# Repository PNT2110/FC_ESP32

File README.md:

# FC_ESP32 Flight Controller

An ESP32-WROOM-32 based flight controller designed for 1S brushed quadcopters.

## Features
- **MCU**: ESP32-WROOM-32 (8MB Flash)
- **IMU**: MPU-6500 (SPI interface)
- **Motor Drivers**: 4x AO3400 MOSFETs for brushed motors
- **Optical Flow**: UART interface for MTF-01P sensor (JST SH1.0 4-pin)
- **Power**: 1S LiPo input, TPS63001 Buck-Boost for 3.3V, TPS61070 Boost for 5V (USB/Optical flow)
- **USB**: USB-C connector with CH340C USB-to-UART bridge
- **Expansion**: I2C and UART1 breakout headers (2.54mm pitch)
- **Battery Monitor**: Built-in voltage divider for telemetry

## Hardware Setup & Pinout
- **Motors**: J4, J5, J6, J7 pads (AO3400 driven)
- **Optical Flow (J2)**: pin 1 GND, pin 2 +5V_FLOW, pin 3 ESP32 TX (GPIO17 → sensor RX), pin 4 ESP32 RX (GPIO16 ← sensor TX). Verify the actual sensor cable orientation.
- **I2C Expansion (J8)**: VCC, GND, SDA (GPIO4), SCL (GPIO22)
- **UART1 Expansion (J9)**: VCC, GND, TX (GPIO14), RX (GPIO32)
- **Programming**: CH340C DTR/RTS auto-download circuit; no physical Boot/Reset buttons are present in the generated BOM.

## Current status

The subsequent datasheet review found B.Cu tracks inside the ESP32 antenna region,
power-layout concerns and incomplete flight features despite clean ERC/DRC.
See `BAO_CAO_KIEM_TRA_MACH.md` and `validation/datasheet_audit/LOG_KIEM_TRA.md`.
The independent antenna check fails; do not interpret the routing checks below as
proof that the design is ready to operate or manufacture.

PCB routing and final ERC/DRC/parity checks passed on 2026-09-14 (KiCad 10.0.6):
zero violations and zero unconnected items. Motor solder pads moved 1.5 mm inward;
J2 faces outward. See `validation/FINAL_REVIEW.md` and `validation/final_3d.png`.
Not released for manufacturing or flight. Motor pitch is
66.8 mm, prop diameter 40 mm, board thickness 0.8 mm. Components are on the front;
copper routing uses both layers. Firmware motor actuation is disabled by default;
see `firmware/README.md`.

## Reproducible hardware workflow

Use system Python with KiCad 10 `pcbnew`, `sexpdata` and Shapely installed.
The generator replaces the working PCB and therefore discards its routing.
Back up a routed board before regenerating.

```sh
/usr/bin/python3 tools/build_fc.py
/usr/bin/python3 tools/prepare_route.py
# Route the new FC_ESP32/FC_ESP32.dsn with Freerouting and save FC_ESP32.ses.
/usr/bin/python3 tools/import_route.py
/usr/bin/python3 tools/finish_copper.py
python3 tools/validate_fc.py
```

`build_fc.py` now includes clearance-preserving placement and updates the BOM and
design coordinates. Session import validates placement before replacing copper.
The legacy `critical_routes.py` and `repair_connections.py` contain assumptions
from the older layout and are not part of this workflow.

On the current machine, prefix system-Python commands with
`PYTHONPATH=/home/pnt/miniconda3/lib/python3.14/site-packages`.
This path is environment-specific. Generation was verified in an isolated copy;
all 72 component placements, orientations, values, footprints and nets matched.

The current SES predates the final repairs: do not import it onto the final PCB.
`validation/final_routed.kicad_pcb` preserves the reviewed routing.
`tools/repair_c3_ground.py` documents the deterministic final copper repair from
`validation/only_c3_ground_remaining.kicad_pcb` to its candidate output.

Open `FC_ESP32/FC_ESP32.kicad_pro` for review. Validation records current ERC,
DRC, netlist parity and source hashes in `FC_ESP32/validation_summary.json` and
returns nonzero on errors. Reports do not replace current/thermal analysis or
bench testing. `gerbers/` contains stale outputs, not an approved release.

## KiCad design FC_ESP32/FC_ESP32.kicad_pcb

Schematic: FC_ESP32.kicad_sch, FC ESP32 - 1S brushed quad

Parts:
C1, C17: 22uF 10V X5R; C_0805_2012Metric
C2, C4, C5, C7, C9, C15, C18: 100nF; C_0402_1005Metric
C3: 1uF; C_0603_1608Metric
C6: 10nF; C_0402_1005Metric
C8: 1uF; C_0402_1005Metric
C11: 1uF 10V; C_0603_1608Metric
C12, C13: 10uF 10V X5R; C_0805_2012Metric
C19: 47uF 10V X5R; C_1206_3216Metric
C21, C22, C23, C24: 100nF 10V; C_0603_1608Metric
D1, D2, D3, D4, D5, D6: SS16
J1: USB4105-GF-A; USB_C
J2: MTF-01P SH1.0; JST_SH_SM04B-SRSS-TB_1x04-1MP_P1.00mm_Horizontal
J3: BAT 1S; Battery_Wire_Pads
J4: M1 + / -; Motor_Wire_Pads
J5: M2 + / -; Motor_Wire_Pads
J6: M3 + / -; Motor_Wire_Pads
J7: M4 + / -; Motor_Wire_Pads
J8: I2C; Header_1x04_P2.54mm
J9: UART1; Header_1x04_P2.54mm
L1: 2.2uH VLF4012-2R2M1R5; L_VLF4012
L2: 4.7uH >=1A shielded; L_4x4
Q1, Q2, Q3, Q4: AO3400
Q5, Q6: MMBT3904
R1, R2, R6, R9, R10: 10k; R_0402_1005Metric
R3, R4: 100k 1%; R_0402_1005Metric
R5: 10R; R_0402_1005Metric
R7, R8: 5.1k 1%; R_0402_1005Metric
R11, R15, R17, R19, R21: 100R; R_0402_1005Metric
R12: 1.8M 1%; R_0402_1005Metric
R13: 200k 1%; R_0402_1005Metric
R16, R18, R20, R22: 100k; R_0402_1005Metric
R23, R24: 4.7k; R_0402_1005Metric
U1: ESP32-WROOM-32 (8MB); ESP32
U2: MPU-6500; MPU6500
U3: CH340C
U4: USBLC6-2SC6; SOT-23-6
U5: TPS63001DRCR; Texas_DRC0010J
U6: TPS61070DDCR; SOT-23-6

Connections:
+3V3: C1.1, C2.1, C9.1, C13.1, J8.1, J9.1, L2.1, R1.1, R2.1, R5.1, R23.1, R24.1, U1.2 (3V3), U3.4 (V3), U3.16 (VCC), U5.1 (VOUT), U5.10 (FB), U6.3 (EN), U6.6 (VBAT)
+3V3_IMU: C5.1, C6.1, C8.1, R5.2, R6.1, U2.8 (VDDIO), U2.13 (VDD)
+5V_FLOW: C17.1, C18.1, J2.2, R12.1, U6.5 (VOUT)
BASE_BOOT: Q6.1, R10.2
BASE_EN: Q5.1, R9.2
BOOST_FB: R12.2, R13.1, U6.4 (FB)
BOOST_SW: L2.2, U6.1 (SW)
BOOT: Q6.3, R2.2, U1.25 (IO0)
BUCK_L1: L1.1, U5.4 (L1)
BUCK_L2: L1.2, U5.2 (L2)
CC1: J1.A5 (CC1), R7.1
CC2: J1.B5 (CC2), R8.1
DTR: Q6.2, R9.1, U3.13 (~DTR)
EN: C3.1, Q5.3, R1.2, U1.3 (EN)
FLOW_RX: J2.4, U1.27 (IO16)
FLOW_TX: J2.3, U1.28 (IO17)
GATE1: Q1.1, R15.2, R16.1
GATE2: Q2.1, R17.2, R18.1
GATE3: Q3.1, R19.2, R20.1
GATE4: Q4.1, R21.2, R22.1
GND: C1.2, C2.2, C3.2, C4.2, C5.2, C6.2, C7.2, C8.2, C9.2, C11.2, C12.2, C13.2, C15.2, C17.2, C18.2, C19.2, J1.A1 (GND), J1.A12 (GND), J1.B1 (GND), J1.B12 (GND), J1.SH (SHIELD), J2.1, J3.2, J8.2, J9.2, Q1.2, Q2.2, Q3.2, Q4.2, R4.2, R7.2, R8.2, R13.2, R16.2, R18.2, R20.2, R22.2, U1.1 (GND), U1.15 (GND), U1.38 (GND), U1.39 (GND), U2.11 (FSYNC), U2.18 (GND), U2.20 (RESV_2), U2.25 (EXP), U3.1 (GND), U3.15 (R232), U4.2 (GND), U5.3 (PGND), U5.9 (GND), U5.11 (PGND), U6.2 (GND)
I2C_SCL: J8.4, R24.2, U1.36 (IO22)
I2C_SDA: J8.3, R23.2, U1.26 (IO4)
IMU_CS: R6.2, U1.33 (IO21), U2.22 (NCS)
IMU_INT: U1.6 (IO34), U2.12 (INT)
M1_NEG: C21.2, D1.2, J4.2, Q1.3
M2_NEG: C22.2, D2.2, J5.2, Q2.3
M3_NEG: C23.2, D3.2, J6.2, Q3.3
M4_NEG: C24.2, D4.2, J7.2, Q4.3
PWM1: R15.1, U1.10 (IO25)
PWM2: R17.1, U1.11 (IO26)
PWM3: R19.1, U1.12 (IO27)
PWM4: R21.1, U1.9 (IO33)
REGOUT: C7.1, U2.10 (REGOUT)
RTS: Q5.2, R10.1, U3.14 (~RTS)
SPI_MISO: U1.31 (IO19), U2.9 (AD0/SDO)
SPI_MOSI: U1.37 (IO23), U2.24 (SDA/SDI)
SPI_SCK: U1.30 (IO18), U2.23 (SCL/SCLK)
UART0_RX: U1.34 (RXD0), U3.2 (TXD)
UART0_TX: U1.35 (TXD0), U3.3 (RXD)
UART1_RX: J9.4, U1.8 (IO32)
UART1_TX: J9.3, U1.13 (IO14)
USB_DM: J1.A7 (D-), J1.B7 (D-), U3.6 (UD-), U4.1 (I/O1), U4.6 (I/O1)
USB_DP: J1.A6 (D+), J1.B6 (D+), U3.5 (UD+), U4.3 (I/O2), U4.4 (I/O2)
VBAT: C19.1, C21.1, C22.1, C23.1, C24.1, D1.1, D2.1, D3.1, D4.1, D5.2, J3.1, J4.1, J5.1, J6.1, J7.1, R3.1
VBAT_ADC: C4.1, R3.2, R4.1, U1.7 (IO35)
VBUS: C11.1, D6.2, J1.A4 (VBUS), J1.A9 (VBUS), J1.B4 (VBUS), J1.B9 (VBUS), U4.5 (VBUS)
VINA: C15.1, R11.2, U5.8 (VINA)
VSYS: C12.1, D5.1, D6.1, R11.1, U5.5 (VIN), U5.6 (EN), U5.7 (PS/SYNC)

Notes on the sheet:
POWER RAILS
MCU / BATTERY SENSE
IMU + FLOW (MPU6500 / J2)
USB / CH340C + AUTO-RESET
POWER 1S (TPS63001 / TPS61070)
MOTORS x4 (AO3400 + SS16)

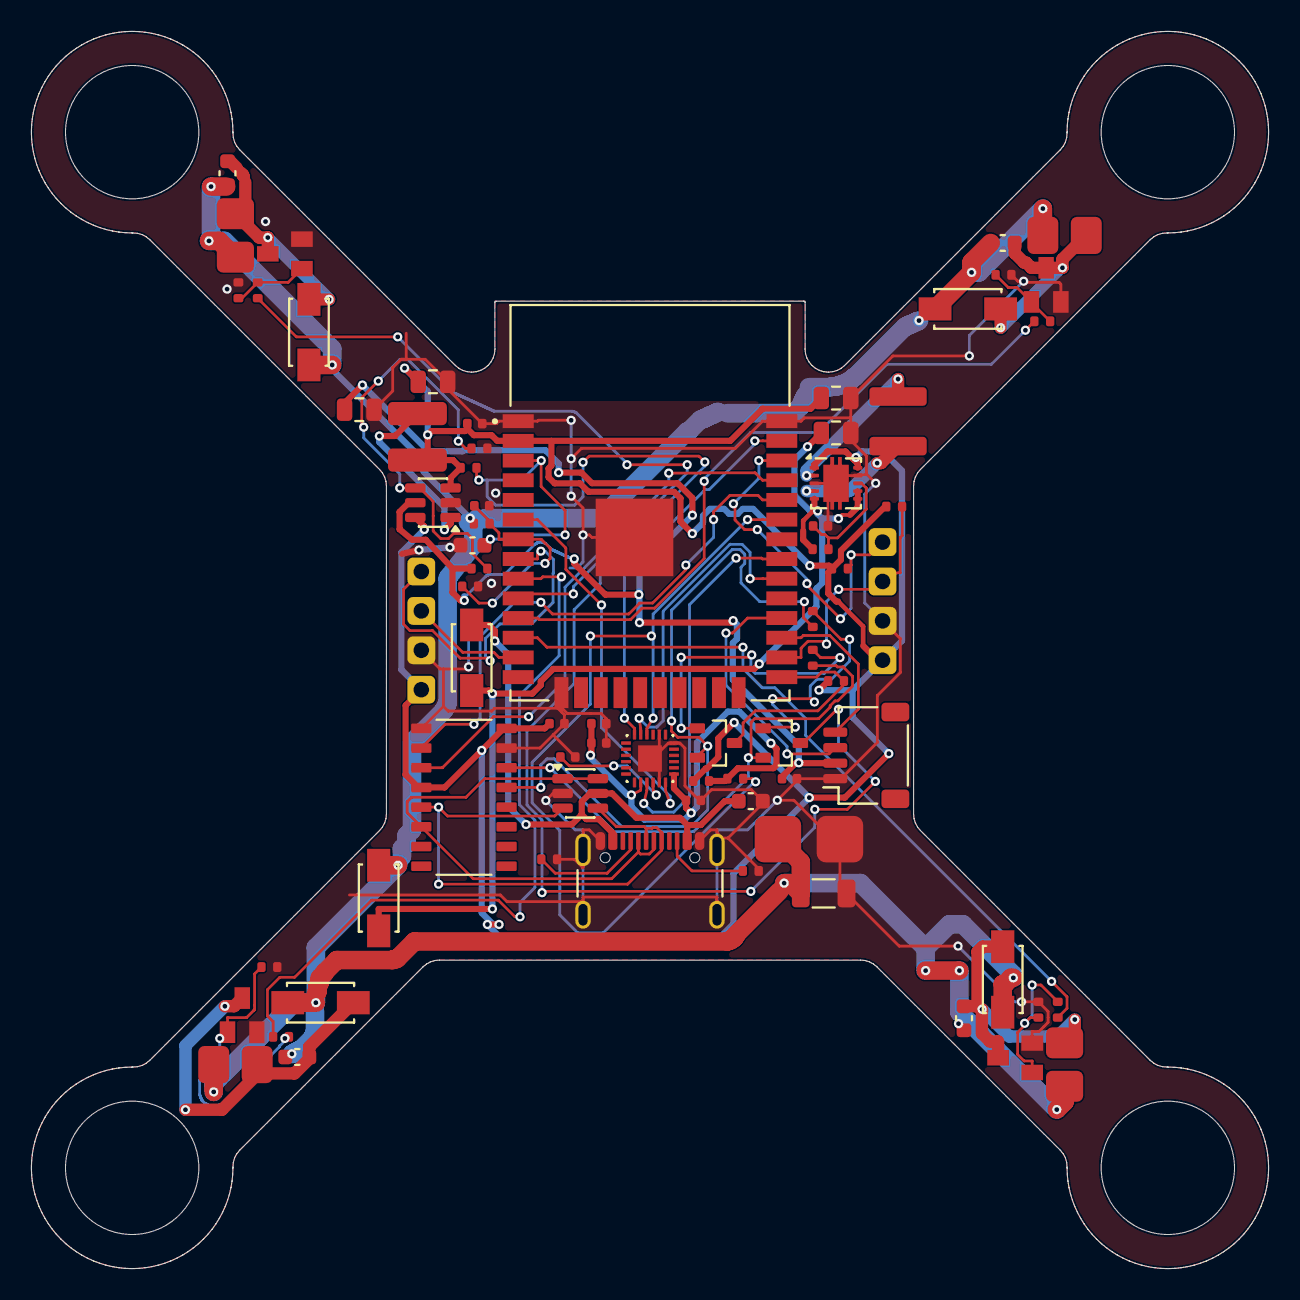
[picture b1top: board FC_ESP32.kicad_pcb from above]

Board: 2 copper layers, 79.8 x 79.8 mm, 76 parts (0 on the bottom side), 49 nets.

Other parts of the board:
H1, H2, H3, H4: (no value)

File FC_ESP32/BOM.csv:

Reference,Value,Footprint,Side,Notes
U1,ESP32-WROOM-32 (8MB),FC_Local:ESP32,F,
C1,22uF 10V X5R,FC_Local:C_0805_2012Metric,F,
C2,100nF,FC_Local:C_0402_1005Metric,F,
R1,10k,FC_Local:R_0402_1005Metric,F,
C3,1uF,FC_Local:C_0603_1608Metric,F,
R2,10k,FC_Local:R_0402_1005Metric,F,
R3,100k 1%,FC_Local:R_0402_1005Metric,F,
R4,100k 1%,FC_Local:R_0402_1005Metric,F,
C4,100nF,FC_Local:C_0402_1005Metric,F,
U2,MPU-6500,FC_Local:MPU6500,F,
R5,10R,FC_Local:R_0402_1005Metric,F,
C5,100nF,FC_Local:C_0402_1005Metric,F,
C6,10nF,FC_Local:C_0402_1005Metric,F,
C7,100nF,FC_Local:C_0402_1005Metric,F,
C8,1uF,FC_Local:C_0402_1005Metric,F,
R6,10k,FC_Local:R_0402_1005Metric,F,
J1,USB4105-GF-A,FC_Local:USB_C,F,
U3,CH340C,FC_Local:CH340C,F,
C9,100nF,FC_Local:C_0402_1005Metric,F,
R7,5.1k 1%,FC_Local:R_0402_1005Metric,F,
R8,5.1k 1%,FC_Local:R_0402_1005Metric,F,
U4,USBLC6-2SC6,FC_Local:SOT-23-6,F,
C11,1uF 10V,FC_Local:C_0603_1608Metric,F,
Q5,MMBT3904,FC_Local:MMBT3904,F,
Q6,MMBT3904,FC_Local:MMBT3904,F,
R9,10k,FC_Local:R_0402_1005Metric,F,
R10,10k,FC_Local:R_0402_1005Metric,F,
J2,MTF-01P SH1.0,FC_Local:JST_SH_SM04B-SRSS-TB_1x04-1MP_P1.00mm_Horizontal,F,Pin 3 to sensor Rx; pin 4 to sensor Tx. Verify cable orientation.
J8,I2C,FC_Local:Header_1x04_P2.54mm,F,
J9,UART1,FC_Local:Header_1x04_P2.54mm,F,
R23,4.7k,FC_Local:R_0402_1005Metric,F,
R24,4.7k,FC_Local:R_0402_1005Metric,F,
J3,BAT 1S,FC_Local:Battery_Wire_Pads,F,
D5,SS16,FC_Local:SS16,F,
D6,SS16,FC_Local:SS16,F,
U5,TPS63001DRCR,FC_Local:Texas_DRC0010J,F,
L1,2.2uH VLF4012-2R2M1R5,FC_Local:L_VLF4012,F,
C12,10uF 10V X5R,FC_Local:C_0805_2012Metric,F,
C13,10uF 10V X5R,FC_Local:C_0805_2012Metric,F,
R11,100R,FC_Local:R_0402_1005Metric,F,
C15,100nF,FC_Local:C_0402_1005Metric,F,
U6,TPS61070DDCR,FC_Local:SOT-23-6,F,
L2,4.7uH >=1A shielded,FC_Local:L_4x4,F,4x4 land; choose matching inductor before ordering
C17,22uF 10V X5R,FC_Local:C_0805_2012Metric,F,
R12,1.8M 1%,FC_Local:R_0402_1005Metric,F,
R13,200k 1%,FC_Local:R_0402_1005Metric,F,
C18,100nF,FC_Local:C_0402_1005Metric,F,
C19,47uF 10V X5R,FC_Local:C_1206_3216Metric,F,
Q1,AO3400,FC_Local:AO3400,F,
D1,SS16,FC_Local:SS16,F,
J4,M1 + / -,FC_Local:Motor_Wire_Pads,F,
R15,100R,FC_Local:R_0402_1005Metric,F,
R16,100k,FC_Local:R_0402_1005Metric,F,
C21,100nF 10V,FC_Local:C_0603_1608Metric,F,
Q2,AO3400,FC_Local:AO3400,F,
D2,SS16,FC_Local:SS16,F,
J5,M2 + / -,FC_Local:Motor_Wire_Pads,F,
R17,100R,FC_Local:R_0402_1005Metric,F,
R18,100k,FC_Local:R_0402_1005Metric,F,
C22,100nF 10V,FC_Local:C_0603_1608Metric,F,
Q3,AO3400,FC_Local:AO3400,F,
D3,SS16,FC_Local:SS16,F,
J6,M3 + / -,FC_Local:Motor_Wire_Pads,F,
R19,100R,FC_Local:R_0402_1005Metric,F,
R20,100k,FC_Local:R_0402_1005Metric,F,
C23,100nF 10V,FC_Local:C_0603_1608Metric,F,
Q4,AO3400,FC_Local:AO3400,F,
D4,SS16,FC_Local:SS16,F,
J7,M4 + / -,FC_Local:Motor_Wire_Pads,F,
R21,100R,FC_Local:R_0402_1005Metric,F,
R22,100k,FC_Local:R_0402_1005Metric,F,
C24,100nF 10V,FC_Local:C_0603_1608Metric,F,
